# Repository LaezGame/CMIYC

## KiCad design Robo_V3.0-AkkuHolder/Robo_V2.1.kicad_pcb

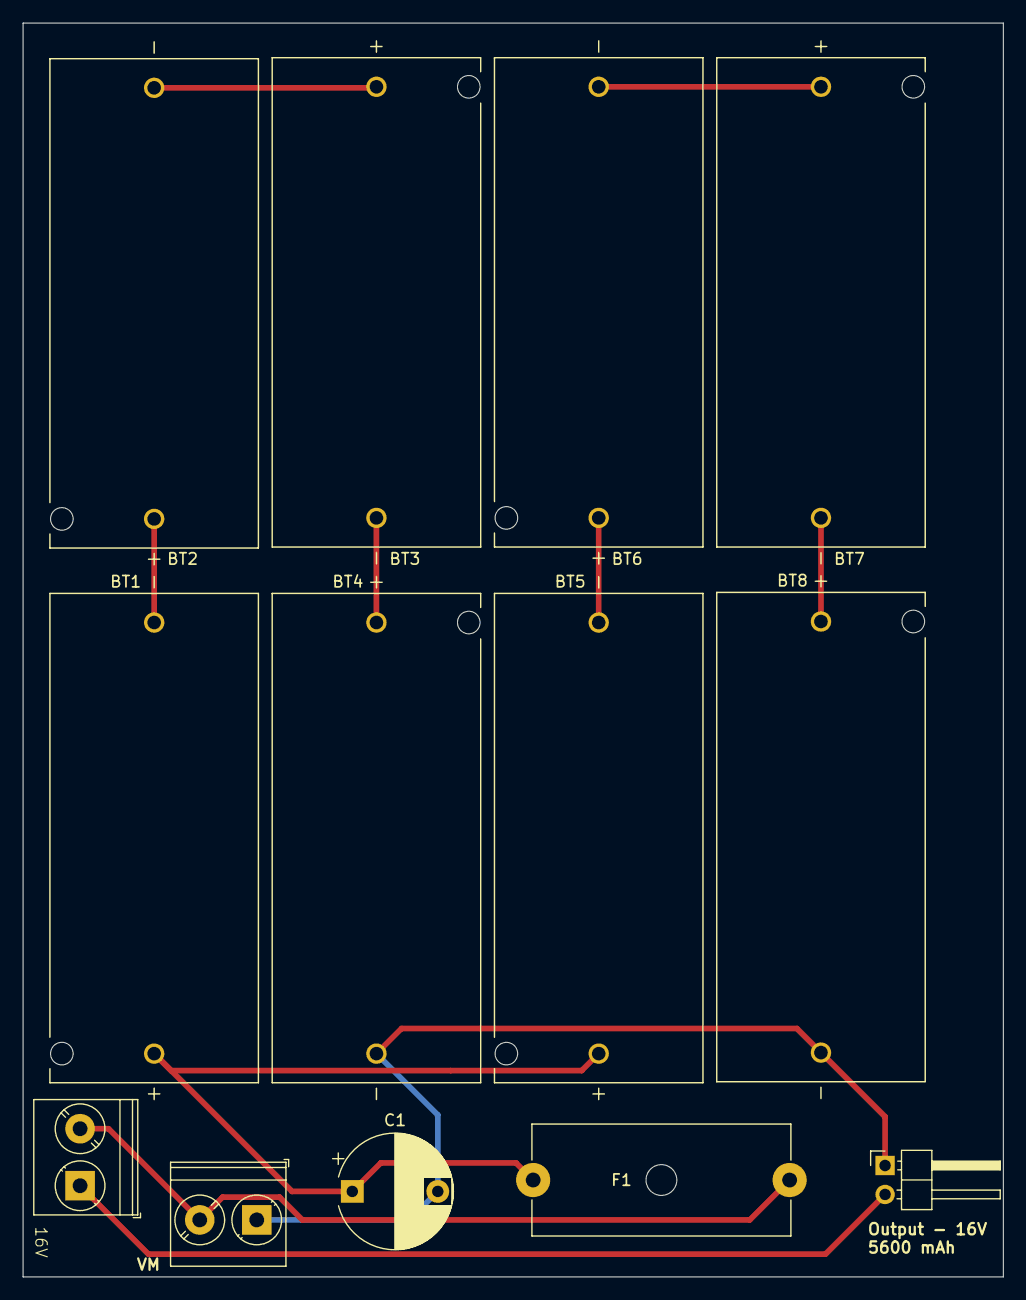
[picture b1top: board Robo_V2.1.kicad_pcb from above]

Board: 2 copper layers, 86.0 x 110.0 mm, 13 parts (0 on the bottom side), 10 nets.

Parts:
BT1, BT2, BT3, BT4, BT5, BT6, BT7, BT8: 1051; BAT_1051
C1: 2mF; CP_Radial_D10.0mm_P7.50mm
F1: Fuse; Fuseholder_Cylinder-5x20mm_Schurter_0031_8201_Horizontal_Op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
Output-16V: 16V; PinHeader_1x02_P2.54mm_Horizontal
SW1: 16V; TerminalBlock_Phoenix_PT-1,5-2-5.0-H_1x02_P5.00mm_Horizontal
VM: Voltmeter_DC; TerminalBlock_Phoenix_PT-1,5-2-5.0-H_1x02_P5.00mm_Horizontal

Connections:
unnamed: BT1.N, BT2.P
unnamed: BT1.P, BT5.P, C1.1, F1.1
unnamed: BT2.N, BT3.P
unnamed: BT3.N, BT4.P
unnamed: BT5.N, BT6.P
unnamed: BT6.N, BT7.P
unnamed: BT7.N, BT8.P
unnamed: F1.2, SW1.2 (B), VM.2 (+)
unnamed: BT4.N, BT8.N, C1.2, Output-16V.1, VM.1 (-)
unnamed: Output-16V.2, SW1.1 (A)

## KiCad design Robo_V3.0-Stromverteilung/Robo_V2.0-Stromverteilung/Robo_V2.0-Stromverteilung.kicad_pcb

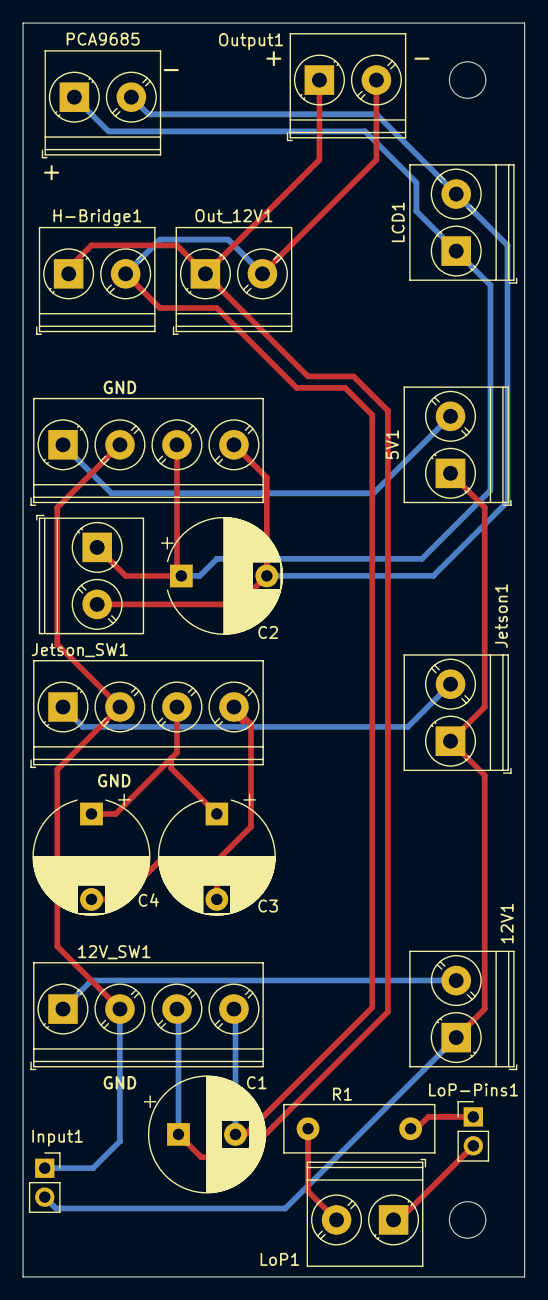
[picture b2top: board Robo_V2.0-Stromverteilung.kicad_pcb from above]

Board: 2 copper layers, 44.0 x 110.0 mm, 22 parts (0 on the bottom side), 14 nets.

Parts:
5V1, 12V1: 16V; TerminalBlock_Phoenix_PT-1,5-2-5.0-H_1x02_P5.00mm_Horizontal
5V_SW2: 5V; TerminalBlock_Phoenix_PT-1,5-4-5.0-H_1x04_P5.00mm_Horizontal
12V_SW1: 12V; TerminalBlock_Phoenix_PT-1,5-4-5.0-H_1x04_P5.00mm_Horizontal
C1: 400uF; CP_Radial_D10.0mm_P5.00mm
C2, C3, C4: 2,2mF; CP_Radial_D10.0mm_P7.50mm
H1, H2: MountingHole; MountingHole_3.2mm_M3
H-Bridge1: 12V; TerminalBlock_Phoenix_PT-1,5-2-5.0-H_1x02_P5.00mm_Horizontal
Input1: 16V; PinSocket_1x02_P2.54mm_Vertical
Jetson1: 16V; TerminalBlock_Phoenix_PT-1,5-2-5.0-H_1x02_P5.00mm_Horizontal
Jetson_SW1: 5V; TerminalBlock_Phoenix_PT-1,5-4-5.0-H_1x04_P5.00mm_Horizontal
LCD1: 5V; TerminalBlock_Phoenix_PT-1,5-2-5.0-H_1x02_P5.00mm_Horizontal
LoP1: 3.3V; TerminalBlock_Phoenix_PT-1,5-2-5.0-H_1x02_P5.00mm_Horizontal
LoP-Pins1: 3.3V; PinHeader_1x02_P2.54mm_Vertical
Out_5V1: 5V; TerminalBlock_Phoenix_PT-1,5-2-5.0-H_1x02_P5.00mm_Horizontal
Out_12V1: 12V; TerminalBlock_Phoenix_PT-1,5-2-5.0-H_1x02_P5.00mm_Horizontal
Output1: 12V; TerminalBlock_Phoenix_PT-1,5-2-5.0-H_1x02_P5.00mm_Horizontal
PCA9685: 5V; TerminalBlock_Phoenix_PT-1,5-2-5.0-H_1x02_P5.00mm_Horizontal
R1: 1000 Ohm; R_Box_L13.0mm_W4.0mm_P9.00mm

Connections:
/5V+: 5V_SW2.3, C2.1, LCD1.1, Out_5V1.1, PCA9685.1
/5V-: 5V_SW2.4, C2.2, LCD1.2, Out_5V1.2, PCA9685.2
/12V+: 12V_SW1.3, C1.1, H-Bridge1.1, Out_12V1.1, Output1.1
/12V-: 12V_SW1.4, C1.2, H-Bridge1.2, Out_12V1.2, Output1.2
/GND: 5V_SW2.2, 12V_SW1.2, Input1.1, Jetson_SW1.2
/Jetson+: C3.1, C4.1, Jetson_SW1.3
/Jetson-: C3.2, C4.2, Jetson_SW1.4
/VCC: 5V1.1 (A), 12V1.1 (A), Input1.2, Jetson1.1 (A)
unnamed: 5V1.2 (B), 5V_SW2.1
unnamed: 12V1.2 (B), 12V_SW1.1
unnamed: Jetson1.2 (B), Jetson_SW1.1
unnamed: LoP1.2 (B), R1.1
unnamed: LoP-Pins1.1, R1.2
unnamed: LoP1.1 (A), LoP-Pins1.2

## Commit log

2023-03-02 Added a bunch of things during the qualification for german open
2025-01-24 chore: Remove unnecessary CMake build files and directories
2025-01-26 Update .vscode/tasks.json to improve task configuration
2025-01-28 Added serial communication written before. Sends serial commands between Jetson Nano and Teensy
2025-01-28 Refactored code to use more functions. Added comments to explain the code better. Added version variable. Increase the version variable when updating.
2025-01-28 Update .gitignore and undistorted-line-recognition.cpp
    - Modify .gitignore to include new rules
    - Update undistorted-line-recognition.cpp with improvements and bug fixes
2025-02-02 Added findPath function - checks if pixels are recognized as line then checks again from there
2025-02-02 Had Copilot clean up the code and add error handling
2025-02-05 fixed errors with string handling and memory
2025-02-06 working serial. very smart
2025-02-09 KiCad
2025-02-10 jetson->teensy
2025-02-10 different serial comm format
2025-02-10 added serial communication with line handling to main program
2025-02-11 Serial kommunikation für Simon
2025-02-12 Implement improved line following
2025-02-12 Create motortest
2025-02-12 added methods for crossing recognition
2025-02-12 implemented motor steering for crossings
